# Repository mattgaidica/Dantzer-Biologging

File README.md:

# What is bio-logging?
The use of miniaturized, animal-borne bio-loggers to make physiological and environmental measurements from free-ranging animals is radically transforming scientific capabilities ([Williams et al., 2019](https://besjournals.onlinelibrary.wiley.com/doi/abs/10.1111/1365-2656.13094)). We have recently explored how to implement these technologies to expand the methods and resolution by which stress and performance are quantified in the wild ([Gaidica & Dantzer, 2019](https://ecoevorxiv.org/huxw6/)).

### Current Challenges
Bio-logging is historically niche due to the unique constraints of field biologists. From fish to birds, it is unreasonable to expect a one-size-fits-all solution. However, the ambitious goals of individuals *can and should* generalize to the bio-logging community under the following headings:

1. _Standardize_ data collection and analysis methods.
2. _Communicate_ approaches and insights.
3. _Innovate_ tools and technologies.

We are doing our best to make our projects **open source**. You can read more about our approach in [the Wiki](https://github.com/mattgaidica/biologging/wiki/Architecture).

## Why squirrels?

The ecological niche occupied by wild squirrels has been conserved for millions of years and is highlighted by their unique adaptations to arboreal life (i.e., in the trees). Their ability to regulate energy and maintain fitness through a variety of natural and imposed challenges ultimately determine their pedigree and survival. Little is known about how the central nervous system (CNS) is involved in these natural behaviors. One of our goals is to use bio-loggers to record from the CNS of wild squirrels to understand how their physiology and behavior are correlated, given the varying demands of their environment. Adding resolution to these important ecological factors is an important consideration to ongoing conservation work, potentially highlighting what ‘optimal adaptations’ are from a physiological perspective.

### Research Platform

Evolutionary pressures on wild animals engender advantageous platforms for study because behavior is so crucially linked with fitness. How mammalian physiology copes and adapts in response to changing environments is an important question that can benefit from the added resolution of bio-loggers. In addition to scientific investigations, the squirrel is a useful model to address many outstanding technical challenges—not unique to ecology—that make long-duration studies in harsh environments possible.

### Kluane Red Squirrel Project
[The Kluane Red Squirrel Project](https://redsquirrel.biology.ualberta.ca) (KRSP) is an interdisciplinary, large-scale field experiment located in the Canadian Yukon. KRSP has been collecting ecological and behavioral data on squirrels since 1987 and conducts a variety of studies and surveys on the population and food availability every year.

Squirrels in the Yukon face intense challenges including drastic changes in light/dark cycles through each season. During the summer months there is very little darkness (see image above). This natural rhythm makes KRSP and the squirrel an ideal candidate to study the affects of circadian entrainment.

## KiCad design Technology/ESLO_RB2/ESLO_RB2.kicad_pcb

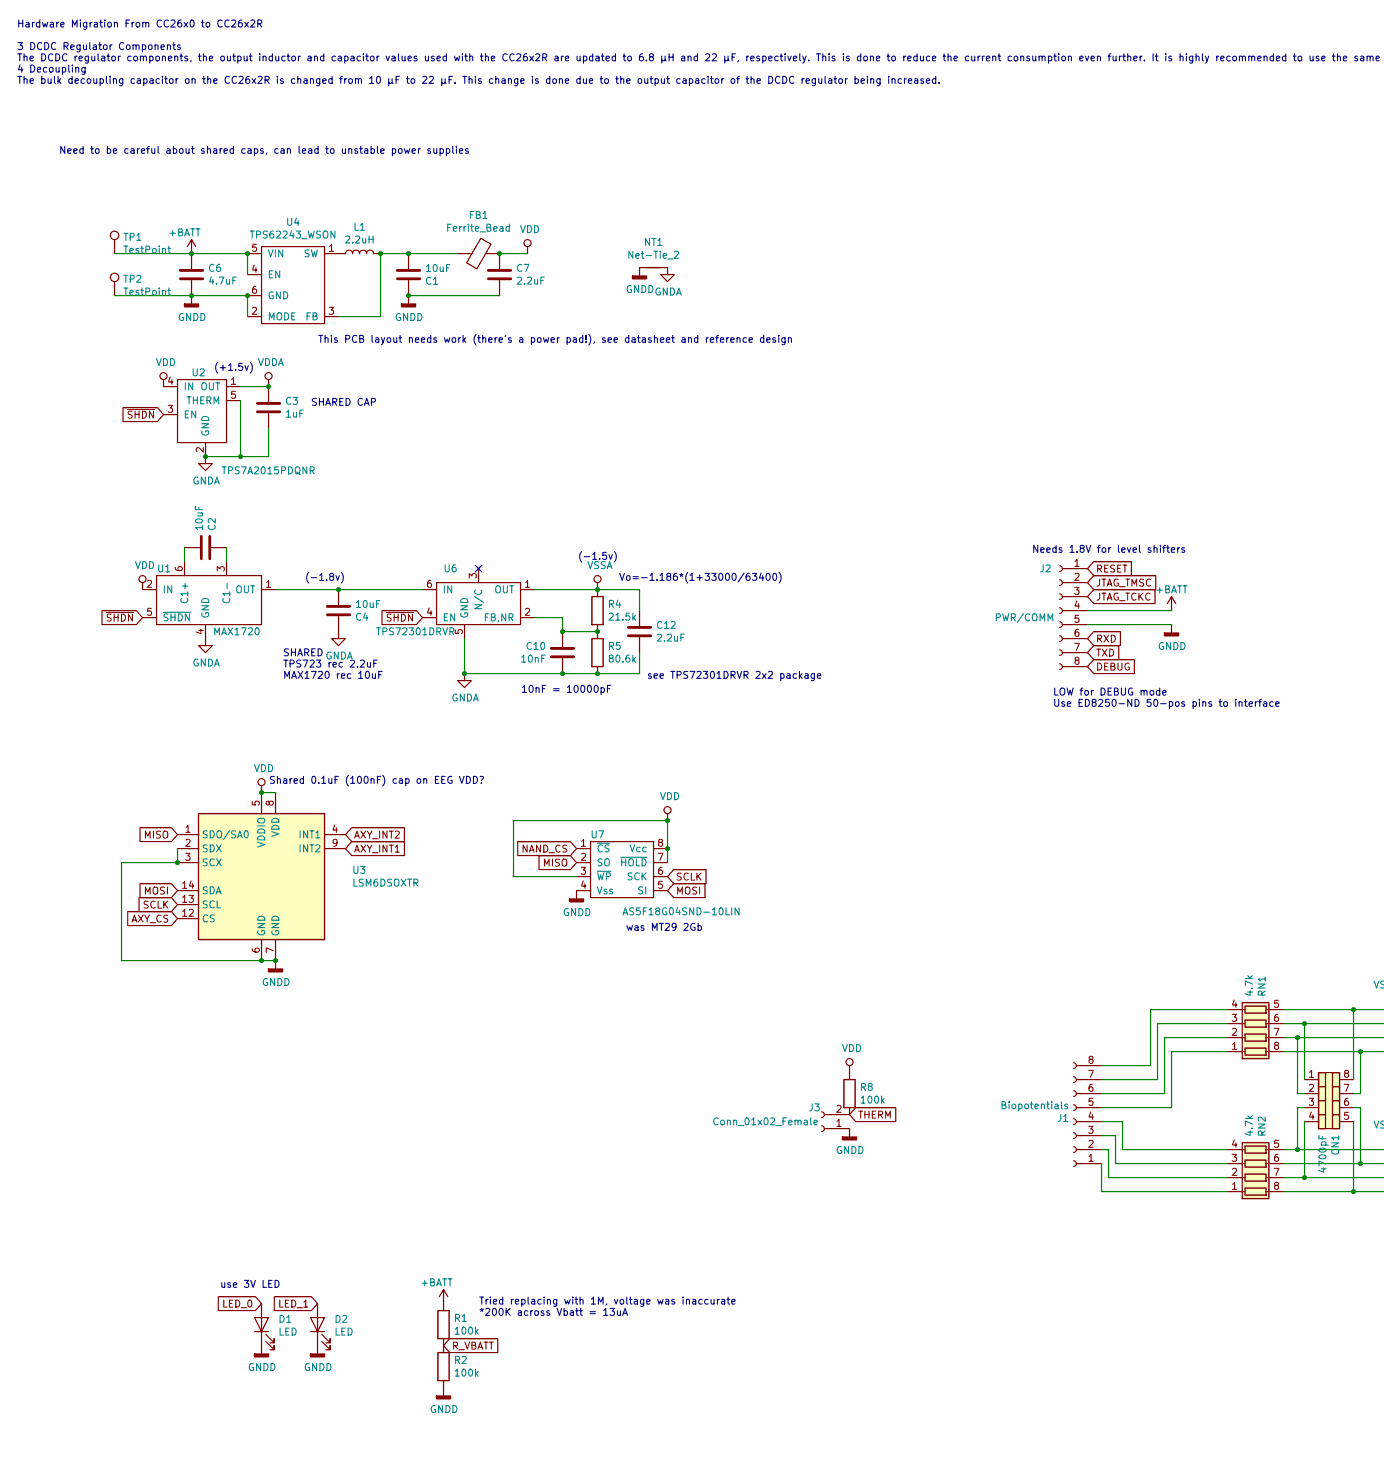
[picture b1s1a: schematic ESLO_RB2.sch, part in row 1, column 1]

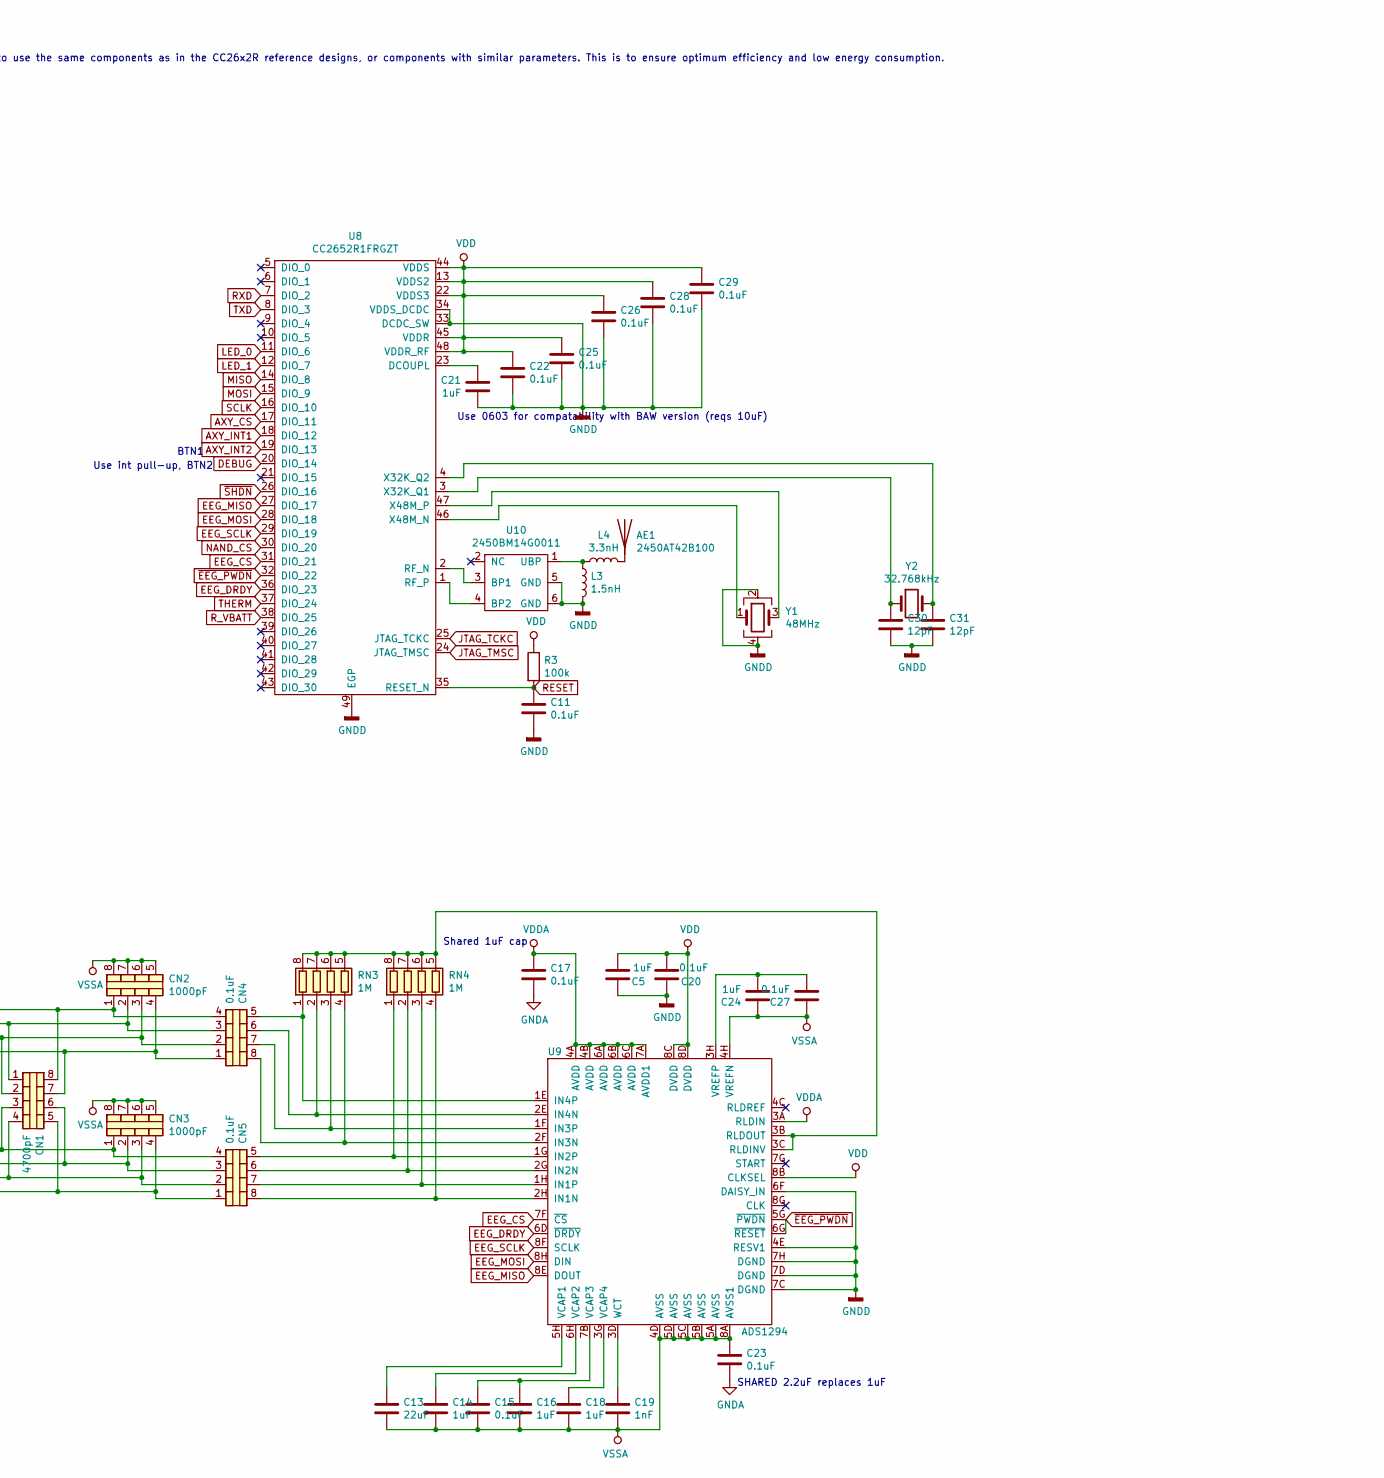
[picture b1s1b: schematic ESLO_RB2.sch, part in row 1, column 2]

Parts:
AE1: 2450AT42B100; Digikey 712-1008-1-ND‎
C1, C2, C4: 10uF; C_0603_1608Metric; Digikey 478-8050-1-ND
C3, C5, C14, C16, C18, C24: 1uF; C_0402_1005Metric; Digikey 399-4873-1-ND
C6: 4.7uF; C_0402_1005Metric; Digikey 1276-1484-2-ND
C7, C12: 2.2uF; C_0402_1005Metric; Digikey 1253-CM05X5R225K10AHCT-ND
C10: 10nF; C_0402_1005Metric; Digikey 1276-1051-1-ND
C11, C15, C17, C20, C22, C23, C25, C26, C27, C28, C29: 0.1uF; C_0402_1005Metric; Digikey 490-6328-1-ND
C13: 22uF; C_0603_1608Metric; Digikey 490-7611-1-ND
C19: 1nF; C_0402_1005Metric; Digikey 478-1101-1-ND
C21: 1uF; C_0603_1608Metric; Digikey 399-7847-2-ND
C30, C31: 12pF; C_0402_1005Metric; Digikey 490-5924-2-ND
CN1: 4700pF; 0612_array; Digikey 399-CA064X473K4RACTUTR-ND
CN2, CN3: 1000pF; 0508_array; Digikey 399-12980-1-ND
CN4, CN5: 0.1uF; 0508_array; Digikey 478-7584-2-ND
D1: LED; LED_0402_1005Metric; Digikey VLMB1500-GS08CT-ND
D2: LED; LED_0402_1005Metric; Digikey VLMO1500-GS08CT-ND
FB1: Ferrite_Bead; C_0603_1608Metric; Digikey 490-5216-2-ND
J1: Biopotentials; ESLO_IO_8_1-27; Digikey ED8250-ND
J2: PWR/COMM; ESLO_IO_8_1-27; Digikey ED90570-ND
J3: Conn_01x02_Female; ESLO_2pin_THERM
L1: 2.2uH; L_0805_2012Metric; Digikey 490-4994-2-ND
L3: 1.5nH; L_0402_1005Metric; Digikey 334-1083-2-ND
L4: 3.3nH; L_0402_1005Metric; Digikey 712-1416-1-ND
NT1: Net-Tie_2; NetTie-2_SMD_Pad0.5mm
R1, R2, R3, R8: 100k; LED_0402_1005Metric; Digikey 311-100KLRCT-ND
R4: 21.5k; R_0402_1005Metric; Digikey RMCF0402FT21K5CT-ND
R5: 80.6k; R_0402_1005Metric; Digikey RMCF0402FT80K6CT-ND
RN1, RN2: 4.7k; 0502_array; Digikey Y6472CT-ND
RN3, RN4: 1M; 0502_array; Digikey Y6105CT-ND
TP1: TestPoint; Half2032Clip_BC-2003; Digikey 36-3036-ND
TP2: TestPoint; 5015_TP; Digikey 36-5015TR-ND
U1: MAX1720; SOT-23-6; Digikey MAX1720EUTGOSCT-ND
U2: TPS7A2015PDQNR; Texas_X2SON-4_1x1mm_P0.65mm; Digikey 296-TPS7A2015PDQNRTR-ND
U3: LSM6DSOXTR; LGA-14_3x2.5mm_P0.5mm_LayoutBorder3x4y; Digikey 497-18367-2-ND
U4: TPS62243_WSON; WSON-6-1EP_2x2mm_P0.65mm_EP1x1.6mm; Digikey 296-46476-1-ND
U6: TPS72301DRVR; WSON-6-1EP_2x2mm_P0.65mm_EP1x1.6mm; Digikey 296-TPS72301DRVRTR-ND
U7: AS5F18G04SND-10LIN; 8x6mm_WSON_UTSO; Digikey 1450-AS5F18G04SND-10LIN-ND
U8: CC2652R1FRGZT; QFN-48-1EP_7x7mm_P0.5mm_EP5.15x5.15mm; Mouser 595-CC2652R1FRGZR
U9: ADS1294; BGA-64_8x8_8.0x8.0mm_ADS129x; Digikey 296-28024-1-ND
U10: 2450BM14G0011; Digikey 712-1620-1-ND
Y1: 48MHz; Crystal_SMD_2016-4Pin_2.0x1.6mm; Digikey 535-13927-2-ND
Y2: 32.768kHz; Crystal_SMD_2012-2Pin_2.0x1.2mm; Digikey SER4081TR-ND

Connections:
+BATT: C6.1, J2.4, R1.1, TP1.1, U4.4 (EN), U4.5 (VIN)
AXY_CS: U3.12 (CS), U8.17 (DIO_11)
AXY_INT1: U3.9 (INT2), U8.18 (DIO_12)
AXY_INT2: U3.4 (INT1), U8.19 (DIO_13)
DEBUG: J2.8, U8.20 (DIO_14)
EEG_CS: U8.31 (DIO_21), U9.7F (~CS)
EEG_DRDY: U8.36 (DIO_23), U9.6D (~DRDY)
EEG_MISO: U8.27 (DIO_17), U9.8E (DOUT)
EEG_MOSI: U8.28 (DIO_18), U9.8H (DIN)
EEG_SCLK: U8.29 (DIO_19), U9.8F (SCLK)
GNDA: C3.2, C4.2, C10.1, C12.2, C17.2, C23.2, NT1.2, R5.2, U1.4 (GND), U2.2 (GND), U2.5 (THERM), U6.5 (GND)
GNDD: C1.2, C5.1, C6.2, C7.2, C11.2, C20.1, C21.1, C22.2, C25.2, C26.2, C28.2, C29.2, C30.2, C31.2, D1.1 (K), D2.1 (K), J2.5, J3.1, L3.2, NT1.1, R2.2, TP2.1, U3.2 (SDX), U3.3 (SCX), U3.6 (GND), U3.7 (GND), U4.2 (MODE), U4.6 (GND), U7.4 (Vss), U8.33 (DCDC_SW), U8.34 (VDDS_DCDC), U8.49 (EGP), U9.4E (RESV1), U9.6F (DAISY_IN), U9.7C (DGND), U9.7D (DGND), U9.7H (DGND), U10.5 (GND), U10.6 (GND), Y1.2, Y1.4
JTAG_TCKC: J2.3, U8.25 (JTAG_TCKC)
JTAG_TMSC: J2.2, U8.24 (JTAG_TMSC)
LED_0: D1.2 (A), U8.11 (DIO_6)
LED_1: D2.2 (A), U8.12 (DIO_7)
MISO: U3.1 (SDO/SA0), U7.2 (SO), U8.14 (DIO_8)
MOSI: U3.14 (SDA), U7.5 (SI), U8.15 (DIO_9)
NAND_CS: U7.1 (~CS), U8.30 (DIO_20)
unnamed: AE1.1, L4.2
unnamed: C1.1, FB1.2, L1.2, U4.3 (FB)
unnamed: C2.1, U1.6 (C1+)
unnamed: C2.2, U1.3 (C1-)
unnamed: C4.1, U1.1 (OUT), U6.6 (IN)
unnamed: C10.2, R4.2, R5.1, U6.2 (FB,NR)
unnamed: C13.1, U9.5H (VCAP1)
unnamed: C14.1, U9.6H (VCAP2)
unnamed: C15.1, C16.1, U9.7B (VCAP3)
unnamed: C18.1, U9.3G (VCAP4)
unnamed: C19.1, U9.3D (WCT)
unnamed: C21.2, U8.23 (DCOUPL)
unnamed: C24.2, C27.2, U9.3H (VREFP)
unnamed: C30.1, U8.3 (X32K_Q1), Y2.1
unnamed: C31.1, U8.4 (X32K_Q2), Y2.2
unnamed: CN1.1 (C1.1), CN2.2 (C2.1), CN4.3 (C3.1), RN1.6 (R3.2)
unnamed: CN1.2 (C2.1), CN2.3 (C3.1), CN4.2 (C2.1), RN1.7 (R2.2)
unnamed: CN1.3 (C3.1), CN3.1 (C1.1), CN5.4 (C4.1), RN2.5 (R4.2)
unnamed: CN1.4 (C4.1), CN3.3 (C3.1), CN5.2 (C2.1), RN2.7 (R2.2)
unnamed: CN1.5 (C4.2), CN3.4 (C4.1), CN5.1 (C1.1), RN2.8 (R1.2)
unnamed: CN1.6 (C3.2), CN3.2 (C2.1), CN5.3 (C3.1), RN2.6 (R3.2)
unnamed: CN1.7 (C2.2), CN2.4 (C4.1), CN4.1 (C1.1), RN1.8 (R1.2)
unnamed: CN1.8 (C1.2), CN2.1 (C1.1), CN4.4 (C4.1), RN1.5 (R4.2)
unnamed: CN4.5 (C4.2), RN3.1 (R1.1), U9.1E (IN4P)
unnamed: CN4.6 (C3.2), RN3.2 (R2.1), U9.2E (IN4N)
unnamed: CN4.7 (C2.2), RN3.3 (R3.1), U9.1F (IN3P)
unnamed: CN4.8 (C1.2), RN3.4 (R4.1), U9.2F (IN3N)
unnamed: CN5.5 (C4.2), RN4.1 (R1.1), U9.1G (IN2P)
unnamed: CN5.6 (C3.2), RN4.2 (R2.1), U9.2G (IN2N)
unnamed: CN5.7 (C2.2), RN4.3 (R3.1), U9.1H (IN1P)
unnamed: CN5.8 (C1.2), RN4.4 (R4.1), U9.2H (IN1N)
unnamed: J1.1, RN2.1 (R1.1)
unnamed: J1.2, RN2.2 (R2.1)
unnamed: J1.3, RN2.3 (R3.1)
unnamed: J1.4, RN2.4 (R4.1)
unnamed: J1.5, RN1.1 (R1.1)
unnamed: J1.6, RN1.2 (R2.1)
unnamed: J1.7, RN1.3 (R3.1)
unnamed: J1.8, RN1.4 (R4.1)
unnamed: L1.1, U4.1 (SW)
unnamed: L3.1, L4.1, U10.1 (UBP)
unnamed: RN3.5 (R4.2), RN3.6 (R3.2), RN3.7 (R2.2), RN3.8 (R1.2), RN4.5 (R4.2), RN4.6 (R3.2), RN4.7 (R2.2), RN4.8 (R1.2), U9.3B (RLDOUT), U9.3C (RLDINV)
unnamed: U8.46 (X48M_N), Y1.1
unnamed: U8.47 (X48M_P), Y1.3
unnamed: U8.2 (RF_N), U10.3 (BP1)
unnamed: U8.1 (RF_P), U10.4 (BP2)
RESET: C11.1, J2.1, R3.2, U8.35 (RESET_N)
RXD: J2.6, U8.7 (DIO_2)
R_VBATT: R1.2, R2.1, U8.38 (DIO_25)
SCLK: U3.13 (SCL), U7.6 (SCK), U8.16 (DIO_10)
THERM: J3.2, R8.2, U8.37 (DIO_24)
TXD: J2.7, U8.8 (DIO_3)
VDD: C5.2, C7.1, C20.2, C22.1, C25.1, C26.1, C28.1, C29.1, FB1.1, R3.1, R8.1, U1.2 (IN), U2.4 (IN), U3.5 (VDDIO), U3.8 (VDD), U7.3 (~WP), U7.7 (~HOLD), U7.8 (Vcc), U8.13 (VDDS2), U8.22 (VDDS3), U8.44 (VDDS), U8.45 (VDDR), U8.48 (VDDR_RF), U9.8B (CLKSEL), U9.8C (DVDD), U9.8D (DVDD)
VDDA: C3.1, C17.1, U2.1 (OUT), U9.3A (RLDIN), U9.4A (AVDD), U9.4B (AVDD), U9.6A (AVDD), U9.6B (AVDD), U9.6C (AVDD), U9.7A (AVDD1)
VSSA: C12.1, C13.2, C14.2, C15.2, C16.2, C18.2, C19.2, C23.1, C24.1, C27.1, CN2.5 (C4.2), CN2.6 (C3.2), CN2.7 (C2.2), CN2.8 (C1.2), CN3.5 (C4.2), CN3.6 (C3.2), CN3.7 (C2.2), CN3.8 (C1.2), R4.1, U6.1 (OUT), U9.4D (AVSS), U9.4H (VREFN), U9.5A (AVSS), U9.5B (AVSS), U9.5C (AVSS), U9.5D (AVSS), U9.8A (AVSS1)
~EEG_PWDN: U8.32 (DIO_22), U9.5G (~PWDN), U9.6G (~RESET)
~SHDN: U1.5 (~SHDN), U2.3 (EN), U6.4 (EN), U8.26 (DIO_16)

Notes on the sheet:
Vo=-1.186*(1+33000/63400)
(-1.5v)
(+1.5v)
(-1.8v)
SHARED TPS723 rec 2.2uF MAX1720 rec 10uF
SHARED CAP
BTN1
Shared 1uF cap
SHARED 2.2uF replaces 1uF
Use int pull-up, BTN2
LOW for DEBUG mode Use ED8250-ND 50-pos pins to interface
Needs 1.8V for level shifters
10nF = 10000pF
Tried replacing with 1M, voltage was inaccurate *200K across Vbatt = 13uA
see TPS72301DRVR 2x2 package
Hardware Migration From CC26x0 to CC26x2R 3 DCDC Regulator Components The DCDC regulator components, the output inductor and capacitor values used with the CC26x2R are updated to 6.8 μH and 22 μF, respectively. This is done to reduce the current consumption even further. It is highly recommended to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
was MT29 2Gb
use 3V LED
Shared 0.1uF (100nF) cap on EEG VDD?
Use 0603 for compatability with BAW version (reqs 10uF)
This PCB layout needs work (there’s a power pad!), see datasheet and reference design
Need to be careful about shared caps, can lead to unstable power supplies

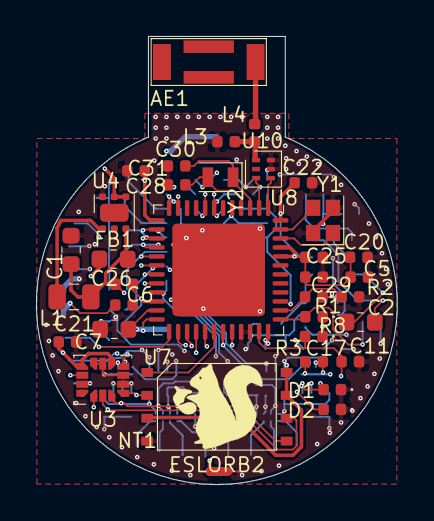
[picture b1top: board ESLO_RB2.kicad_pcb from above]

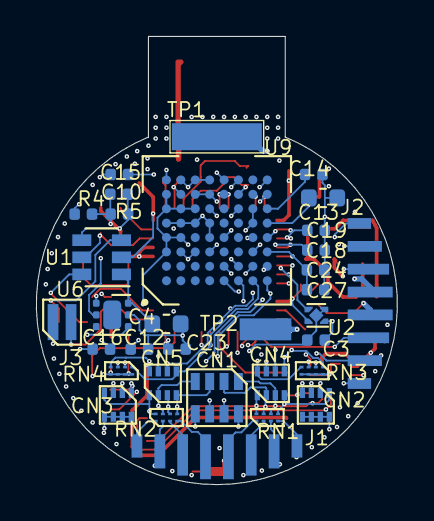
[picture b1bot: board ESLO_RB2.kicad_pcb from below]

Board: 4 copper layers, 20.0 x 24.9 mm, 68 parts (33 on the bottom side), 76 nets.

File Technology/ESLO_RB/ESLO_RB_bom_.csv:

Component,Description,Part,References,Value,Footprint,Quantity Per PCB,Datasheet,Digikey,Mouser
1,Antenna,Antenna,AE1,2450AT42B100,2450AT42B100,1,~,712-1008-1-ND‎,
2,Unpolarized capacitor,C,C3 C11 C15 C17 C20 C22 C23 C25 C26 C27 C28 C29,0.1uF,C_0402_1005Metric,12,~,490-6328-1-ND,
3,Unpolarized capacitor,C,C7,0.22uF,C_0402_1005Metric,1,~,1276-1176-1-ND,
4,Unpolarized capacitor,C,C10,10nF,C_0402_1005Metric,1,~,1276-1051-1-ND,
5,Unpolarized capacitor,C,C1 C2 C4 C6,10uF,C_0603_1608Metric,4,~,490-14372-1-ND,
6,Unpolarized capacitor,C,C19,1nF,C_0402_1005Metric,1,~,478-1101-1-ND,
7,Unpolarized capacitor,C,C5 C9 C14 C16 C18 C21 C24,1uF,C_0402_1005Metric,7,~,399-4873-1-ND,
8,Unpolarized capacitor,C,C8 C12,2.2uF,C_0402_1005Metric,2,~,1276-1469-1-ND,
9,Unpolarized capacitor,C,C13,22uF,C_0603_1608Metric,1,~,1276-2867-1-ND,
10,"4 capacitor network, parallel topology, DIP package",C_Pack04,CN2 CN3,1000pF,0508_array,2,~,478-W2A45C102KAT2ACT-ND,
11,"4 capacitor network, parallel topology, DIP package",C_Pack04,CN4 CN5,1uF,0508_array,2,~,,581-W2L16D105MAT1A
12,"4 capacitor network, parallel topology, DIP package",C_Pack04,CN1,4700pF,0508_array,1,~,,581-W2A41C472KAT2A
13,Light emitting diode,LED,D1,LED,LED_0603_1608Metric,1,~,SML-D12V1WT86CT-ND,
14,"Generic connector, single row, 01x10, script generated (kicad-library-utils/schlib/autogen/connector/)",Conn_01x10_Female,J1,10POS Biopotentials,ARBO_IO10_1.27mm,1,~,ED10276-ND,
15,"Generic connector, single row, 01x06, script generated (kicad-library-utils/schlib/autogen/connector/)",Conn_01x06_Female,J2,6POS Power/JTAG,ARBO_IO6_1.27mm,1,~,ED10273-ND,
16,Inductor,L,L3,1.5nH,L_0402_1005Metric,1,~,712-1411-1-ND,
17,Inductor,L,L1,2.2uH,L_0805_2012Metric,1,~,490-7781-1-ND,
18,Inductor,L,L4,3.3nH,L_0402_1005Metric,1,~,712-1416-1-ND,
19,Inductor,L,L2,BLM18HE152SN1,L_0603_1608Metric,1,~,490-5216-1-ND,
20,"Net tie, 2 pins",Net-Tie_2,NT1,Net-Tie_2,NetTie-2_SMD_Pad0.5mm,1,~,,
21,Resistor,R,R1 R2 R3 R8,100k,LED_0402_1005Metric,4,~,311-100KLRCT-ND,
22,Resistor,R,R4,21.5k,R_0402_1005Metric,1,~,RMCF0402FT21K5CT-ND,
23,Resistor,R,R6 R7,4.7k,R_0402_1005Metric,2,~,311-4.7KJRCT-ND,
24,Resistor,R,R5,80.6k,R_0402_1005Metric,1,~,RMCF0402FT80K6CT-ND,
25,"4 resistor network, parallel topology, DIP package",R_Pack04,RN3 RN4,1M,0502_array,2,~,Y6105CT-ND,
26,"4 resistor network, parallel topology, DIP package",R_Pack04,RN1 RN2,4.7k,0502_array,2,~,Y6472CT-ND,
27,,2450BM14G0011,U10,2450BM14G0011,2450BM14G0011,1,,712-1620-1-ND,
28,,ADS1294,U9,ADS1294,BGA-64_8x8_8.0x8.0mm_ADS129x,1,,296-28024-1-ND,
29,,CC2652RB,U8,CC2652RB,QFN-48-1EP_7x7mm_P0.5mm_EP5.15x5.15mm,1,,296-CC2652RB1FRGZRCT-ND,
30,"FRAM memory with SPI interface, SOIC-8 SON-8",MB85RS2MT,U3,CY15V104QI-20LPXC,8-GQFN_FRAM_3.28mm-3.23mm,1,http://www.fujitsu.com/downloads/MICRO/fsa/pdf/products/memo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,428-4724-ND,
31,"250-mA Ultra-Low-Noise Low-IQ LDO, 1.8V, SOT-23",LP5907MFX-1.8,U5,LP5907MFX-1.5,SOT-23-5,1,http://www.ti.com/lit/ds/symlink/lp5907.pdf,296-40355-1-ND,
32,,LSM303AGR,U4,LSM303AGR,LGA-12_2x2mm_P0.5mm,1,,497-16527-1-ND,
33,,MAX1720,U1,MAX1720,SOT-23-6,1,,MAX1720EUTGOSCT-ND,
34,,IS37SML01G1,U7,MT29F2G01ABBGDWB-IT:G TR,8x6mm_WSON_UTSO,1,,557-1665-1-ND,
35,,TPS62740,U2,TPS62740,WSON-12-1EP_3x2mm_P0.5mm_EP1x2.65,1,,296-39459-1-ND,
36,,TPS72325,U6,TPS72301DDCT,SOT-23-5,1,,296-38438-1-ND,





Component Groups:,36
Component Count:,65
Fitted Components:,65
Number of PCBs:,1
Total components:,65
Schematic Version:,
Schematic Date:,
BoM Date:,"Friday, June 04, 2021 at 01:24:00 PM"
Schematic Source:,/Users/matt/Box Sync/Biologging/Technology/ESLO_RB/ESLO_RB.sch
KiCad Version:,Eeschema (5.1.5-0-10_14)

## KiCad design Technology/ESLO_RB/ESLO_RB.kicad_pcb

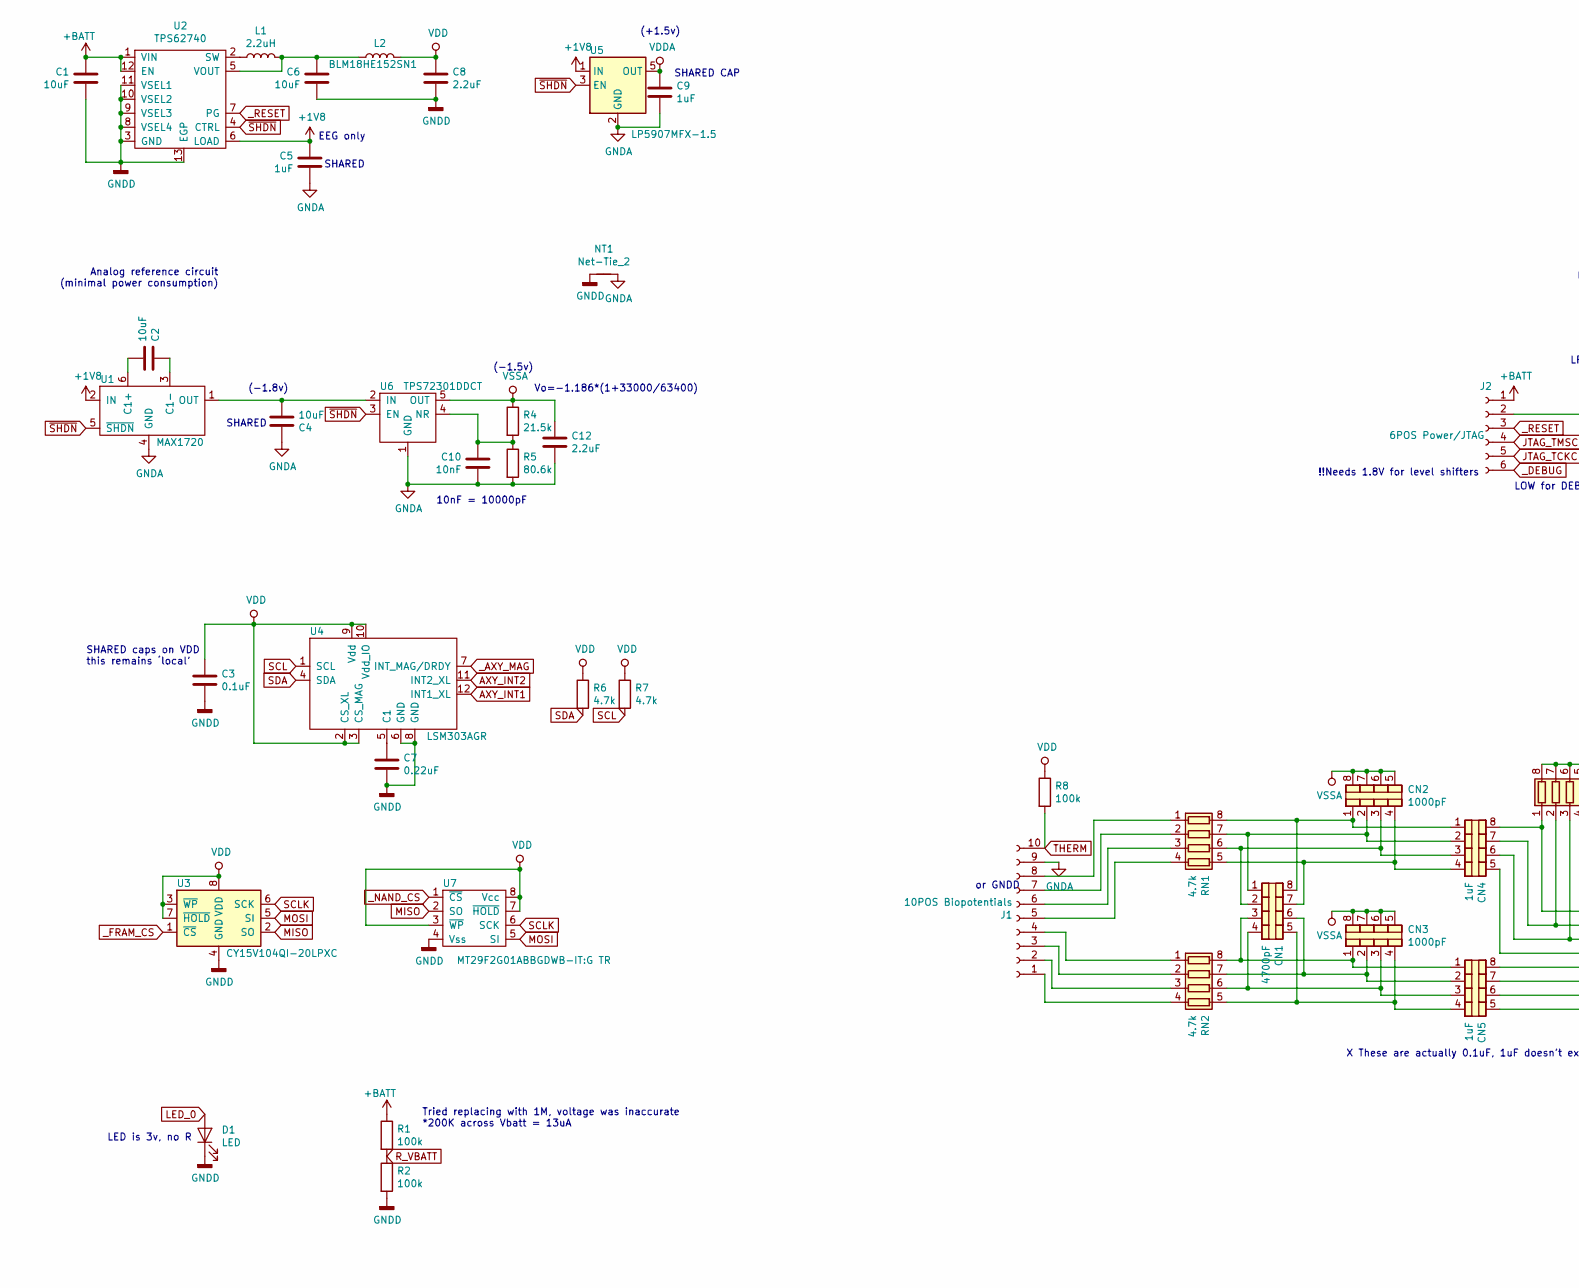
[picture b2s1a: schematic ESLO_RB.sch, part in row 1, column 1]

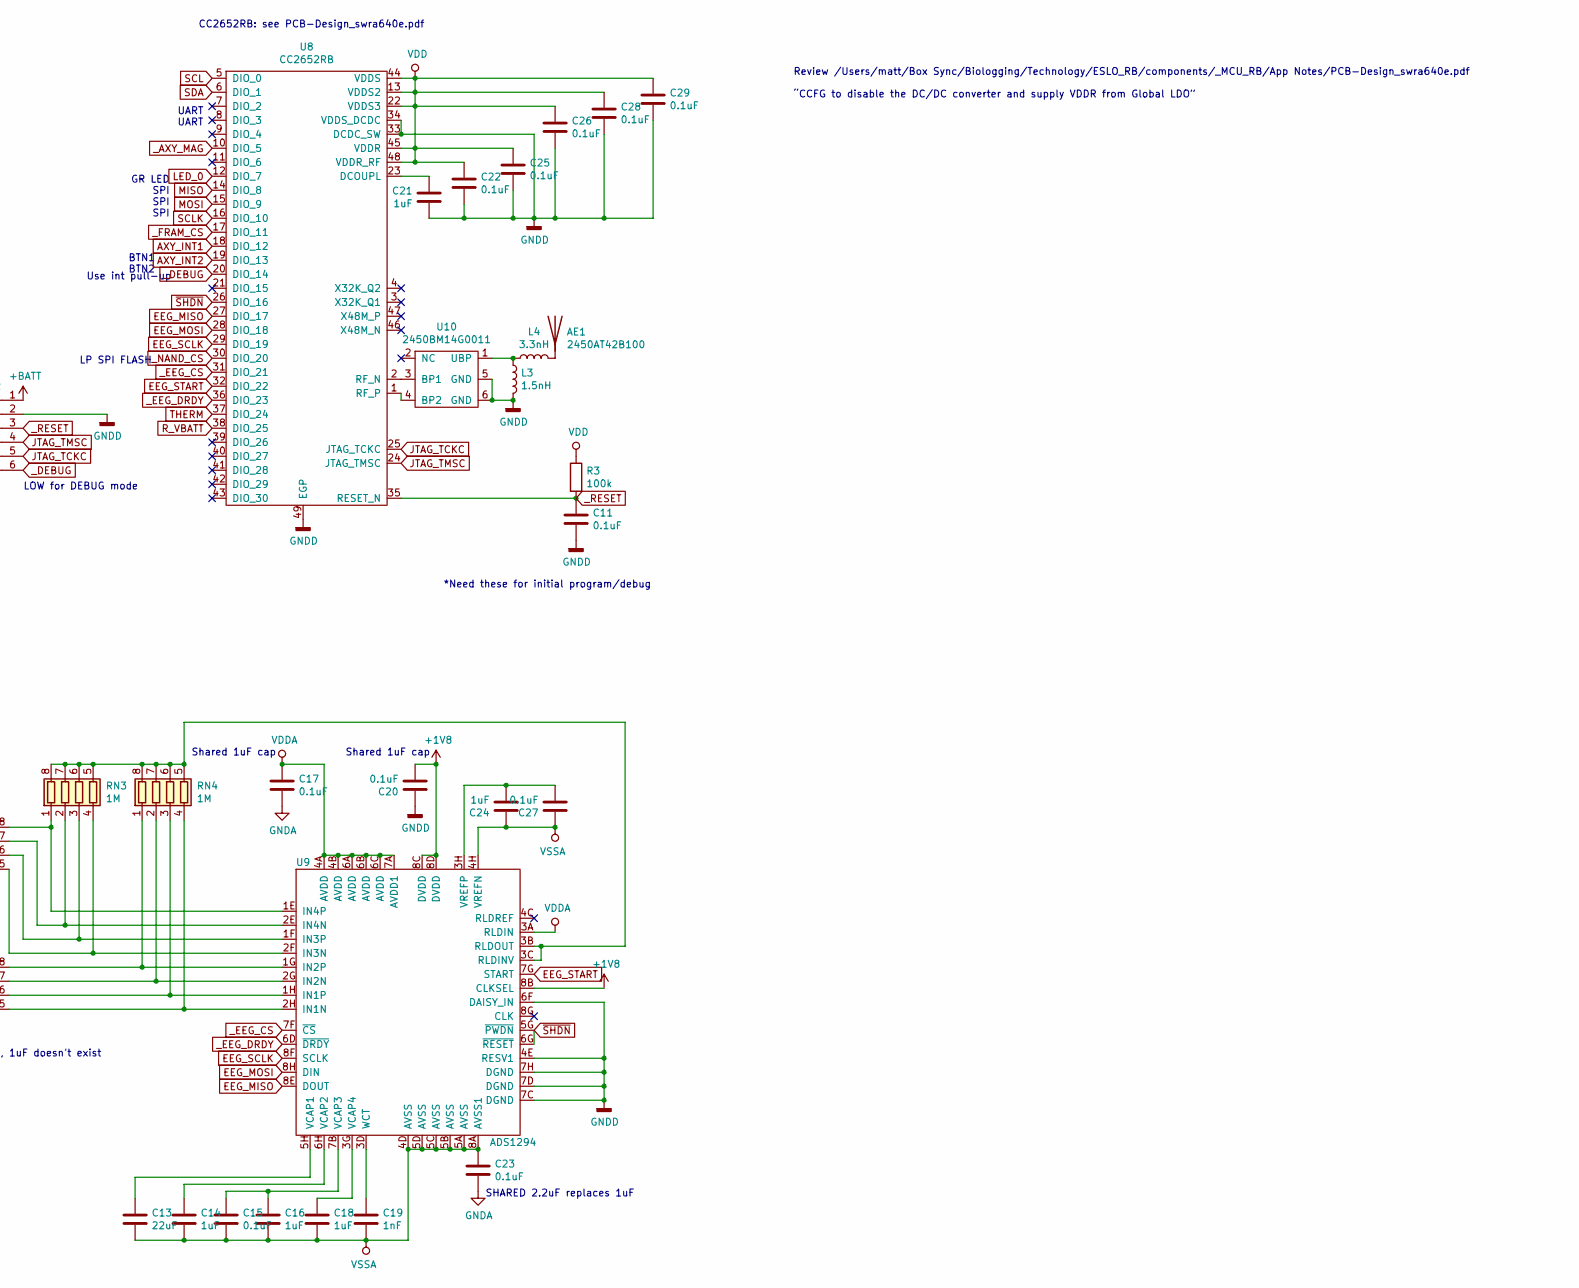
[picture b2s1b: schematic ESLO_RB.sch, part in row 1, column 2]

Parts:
AE1: 2450AT42B100; Digikey 712-1008-1-ND‎
C1, C2, C4, C6: 10uF; C_0603_1608Metric; Digikey 490-14372-1-ND
C3, C11, C15, C17, C20, C22, C23, C25, C26, C27, C28, C29: 0.1uF; C_0402_1005Metric; Digikey 490-6328-1-ND
C5, C9, C14, C16, C18, C21, C24: 1uF; C_0402_1005Metric; Digikey 399-4873-1-ND
C7: 0.22uF; C_0402_1005Metric; Digikey 1276-1176-1-ND
C8, C12: 2.2uF; C_0402_1005Metric; Digikey 1276-1469-1-ND
C10: 10nF; C_0402_1005Metric; Digikey 1276-1051-1-ND
C13: 22uF; C_0603_1608Metric; Digikey 1276-2867-1-ND
C19: 1nF; C_0402_1005Metric; Digikey 478-1101-1-ND
CN1: 4700pF; 0508_array; Mouser 581-W2A41C472KAT2A
CN2, CN3: 1000pF; 0508_array; Digikey 478-W2A45C102KAT2ACT-ND
CN4, CN5: 1uF; 0508_array; Mouser 581-W2L16D105MAT1A
D1: LED; LED_0603_1608Metric; Digikey SML-D12V1WT86CT-ND
J1: 10POS Biopotentials; ARBO_IO10_1.27mm; Digikey ED10276-ND
J2: 6POS Power/JTAG; ARBO_IO6_1.27mm; Digikey ED10273-ND
L1: 2.2uH; L_0805_2012Metric; Digikey 490-7781-1-ND
L2: BLM18HE152SN1; L_0603_1608Metric; Digikey 490-5216-1-ND
L3: 1.5nH; L_0402_1005Metric; Digikey 712-1411-1-ND
L4: 3.3nH; L_0402_1005Metric; Digikey 712-1416-1-ND
NT1: Net-Tie_2; NetTie-2_SMD_Pad0.5mm
R1, R2, R3, R8: 100k; LED_0402_1005Metric; Digikey 311-100KLRCT-ND
R4: 21.5k; R_0402_1005Metric; Digikey RMCF0402FT21K5CT-ND
R5: 80.6k; R_0402_1005Metric; Digikey RMCF0402FT80K6CT-ND
R6, R7: 4.7k; R_0402_1005Metric; Digikey 311-4.7KJRCT-ND
RN1, RN2: 4.7k; 0502_array; Digikey Y6472CT-ND
RN3, RN4: 1M; 0502_array; Digikey Y6105CT-ND
U1: MAX1720; SOT-23-6; Digikey MAX1720EUTGOSCT-ND
U2: TPS62740; WSON-12-1EP_3x2mm_P0.5mm_EP1x2.65; Digikey 296-39459-1-ND
U3: CY15V104QI-20LPXC; 8-GQFN_FRAM_3.28mm-3.23mm; Digikey 428-4724-ND
U4: LSM303AGR; LGA-12_2x2mm_P0.5mm; Digikey 497-16527-1-ND
U5: LP5907MFX-1.5; SOT-23-5; Digikey 296-40355-1-ND
U6: TPS72301DDCT; SOT-23-5; Digikey 296-38438-1-ND
U7: MT29F2G01ABBGDWB-IT:G TR; 8x6mm_WSON_UTSO; Digikey 557-1665-1-ND
U8: CC2652RB; QFN-48-1EP_7x7mm_P0.5mm_EP5.15x5.15mm; Digikey 296-CC2652RB1FRGZRCT-ND
U9: ADS1294; BGA-64_8x8_8.0x8.0mm_ADS129x; Digikey 296-28024-1-ND
U10: 2450BM14G0011; Digikey 712-1620-1-ND

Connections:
+1V8: C5.2, C20.2, U1.2 (IN), U2.6 (LOAD), U5.1 (IN), U9.8B (CLKSEL), U9.8C (DVDD), U9.8D (DVDD)
+BATT: C1.2, J2.1, R1.1, U2.1 (VIN), U2.12 (EN)
AXY_INT1: U4.12 (INT1_XL), U8.18 (DIO_12)
AXY_INT2: U4.11 (INT2_XL), U8.19 (DIO_13)
EEG_MISO: U8.27 (DIO_17), U9.8E (DOUT)
EEG_MOSI: U8.28 (DIO_18), U9.8H (DIN)
EEG_SCLK: U8.29 (DIO_19), U9.8F (SCLK)
EEG_START: U8.32 (DIO_22), U9.7G (START)
GNDA: C4.2, C5.1, C9.2, C10.1, C12.2, C17.2, C23.2, J1.9, NT1.2, R5.2, U1.4 (GND), U5.2 (GND), U6.1 (GND)
GNDD: C1.1, C3.2, C6.1, C7.1, C8.2, C11.2, C20.1, C21.1, C22.2, C25.2, C26.2, C28.2, C29.2, D1.1 (K), J2.2, L3.2, NT1.1, R2.2, U2.3 (GND), U2.8 (VSEL4), U2.9 (VSEL3), U2.10 (VSEL2), U2.11 (VSEL1), U2.13 (EGP), U3.4 (GND), U4.6 (GND), U4.8 (GND), U7.4 (Vss), U8.33 (DCDC_SW), U8.34 (VDDS_DCDC), U8.49 (EGP), U9.4E (RESV1), U9.6F (DAISY_IN), U9.7C (DGND), U9.7D (DGND), U9.7H (DGND), U10.5 (GND), U10.6 (GND)
JTAG_TCKC: J2.5, U8.25 (JTAG_TCKC)
JTAG_TMSC: J2.4, U8.24 (JTAG_TMSC)
LED_0: D1.2 (A), U8.12 (DIO_7)
MISO: U3.2 (SO), U7.2 (SO), U8.14 (DIO_8)
MOSI: U3.5 (SI), U7.5 (SI), U8.15 (DIO_9)
unnamed: AE1.1, L4.2
unnamed: C2.1, U1.6 (C1+)
unnamed: C2.2, U1.3 (C1-)
unnamed: C4.1, U1.1 (OUT), U6.2 (IN)
unnamed: C6.2, L1.2, L2.1, U2.5 (VOUT)
unnamed: C7.2, U4.5 (C1)
unnamed: C10.2, R4.2, R5.1, U6.4 (NR)
unnamed: C13.1, U9.5H (VCAP1)
unnamed: C14.1, U9.6H (VCAP2)
unnamed: C15.1, C16.1, U9.7B (VCAP3)
unnamed: C18.1, U9.3G (VCAP4)
unnamed: C19.1, U9.3D (WCT)
unnamed: C21.2, U8.23 (DCOUPL)
unnamed: C24.2, C27.2, U9.3H (VREFP)
unnamed: CN1.1 (C1.1), CN2.2 (C2.1), CN4.2 (C2.1), RN1.7 (R2.2)
unnamed: CN1.2 (C2.1), CN2.3 (C3.1), CN4.3 (C3.1), RN1.6 (R3.2)
unnamed: CN1.3 (C3.1), CN3.1 (C1.1), CN5.1 (C1.1), RN2.8 (R1.2)
unnamed: CN1.4 (C4.1), CN3.3 (C3.1), CN5.3 (C3.1), RN2.6 (R3.2)
unnamed: CN1.5 (C4.2), CN3.4 (C4.1), CN5.4 (C4.1), RN2.5 (R4.2)
unnamed: CN1.6 (C3.2), CN3.2 (C2.1), CN5.2 (C2.1), RN2.7 (R2.2)
unnamed: CN1.7 (C2.2), CN2.4 (C4.1), CN4.4 (C4.1), RN1.5 (R4.2)
unnamed: CN1.8 (C1.2), CN2.1 (C1.1), CN4.1 (C1.1), RN1.8 (R1.2)
unnamed: CN4.5 (C4.2), RN3.4 (R4.1), U9.2F (IN3N)
unnamed: CN4.6 (C3.2), RN3.3 (R3.1), U9.1F (IN3P)
unnamed: CN4.7 (C2.2), RN3.2 (R2.1), U9.2E (IN4N)
unnamed: CN4.8 (C1.2), RN3.1 (R1.1), U9.1E (IN4P)
unnamed: CN5.5 (C4.2), RN4.4 (R4.1), U9.2H (IN1N)
unnamed: CN5.6 (C3.2), RN4.3 (R3.1), U9.1H (IN1P)
unnamed: CN5.7 (C2.2), RN4.2 (R2.1), U9.2G (IN2N)
unnamed: CN5.8 (C1.2), RN4.1 (R1.1), U9.1G (IN2P)
unnamed: J1.1, RN2.4 (R4.1)
unnamed: J1.2, RN2.3 (R3.1)
unnamed: J1.3, RN2.2 (R2.1)
unnamed: J1.4, RN2.1 (R1.1)
unnamed: J1.5, RN1.4 (R4.1)
unnamed: J1.6, RN1.3 (R3.1)
unnamed: J1.7, RN1.2 (R2.1)
unnamed: J1.8, RN1.1 (R1.1)
unnamed: L1.1, U2.2 (SW)
unnamed: L3.1, L4.1, U10.1 (UBP)
unnamed: RN3.5 (R4.2), RN3.6 (R3.2), RN3.7 (R2.2), RN3.8 (R1.2), RN4.5 (R4.2), RN4.6 (R3.2), RN4.7 (R2.2), RN4.8 (R1.2), U9.3B (RLDOUT), U9.3C (RLDINV)
unnamed: U8.2 (RF_N), U10.3 (BP1)
unnamed: U8.1 (RF_P), U10.4 (BP2)
R_VBATT: R1.2, R2.1, U8.38 (DIO_25)
SCL: R7.2, U4.1 (SCL), U8.5 (DIO_0)
SCLK: U3.6 (SCK), U7.6 (SCK), U8.16 (DIO_10)
SDA: R6.2, U4.4 (SDA), U8.6 (DIO_1)
THERM: J1.10, R8.2, U8.37 (DIO_24)
VDD: C3.1, C8.1, C22.1, C25.1, C26.1, C28.1, C29.1, L2.2, R3.1, R6.1, R7.1, R8.1, U3.3 (~WP), U3.7 (~HOLD), U3.8 (VDD), U4.2 (CS_XL), U4.3 (CS_MAG), U4.9 (Vdd), U4.10 (Vdd_IO), U7.3 (~WP), U7.7 (~HOLD), U7.8 (Vcc), U8.13 (VDDS2), U8.22 (VDDS3), U8.44 (VDDS), U8.45 (VDDR), U8.48 (VDDR_RF)
VDDA: C9.1, C17.1, U5.5 (OUT), U9.3A (RLDIN), U9.4A (AVDD), U9.4B (AVDD), U9.6A (AVDD), U9.6B (AVDD), U9.6C (AVDD), U9.7A (AVDD1)
VSSA: C12.1, C13.2, C14.2, C15.2, C16.2, C18.2, C19.2, C23.1, C24.1, C27.1, CN2.5 (C4.2), CN2.6 (C3.2), CN2.7 (C2.2), CN2.8 (C1.2), CN3.5 (C4.2), CN3.6 (C3.2), CN3.7 (C2.2), CN3.8 (C1.2), R4.1, U6.5 (OUT), U9.4D (AVSS), U9.4H (VREFN), U9.5A (AVSS), U9.5B (AVSS), U9.5C (AVSS), U9.5D (AVSS), U9.8A (AVSS1)
_AXY_MAG: U4.7 (INT_MAG/DRDY), U8.10 (DIO_5)
_DEBUG: J2.6, U8.20 (DIO_14)
_EEG_CS: U8.31 (DIO_21), U9.7F (~CS)
_EEG_DRDY: U8.36 (DIO_23), U9.6D (~DRDY)
_FRAM_CS: U3.1 (~CS), U8.17 (DIO_11)
_NAND_CS: U7.1 (~CS), U8.30 (DIO_20)
_RESET: C11.1, J2.3, R3.2, U2.7 (PG), U8.35 (RESET_N)
~SHDN: U1.5 (~SHDN), U2.4 (CTRL), U5.3 (EN), U6.3 (EN), U8.26 (DIO_16), U9.5G (~PWDN), U9.6G (~RESET)

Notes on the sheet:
Vo=-1.186*(1+33000/63400)
(-1.5v)
(+1.5v)
(-1.8v)
Analog reference circuit (minimal power consumption)
EEG only
Review /Users/matt/Box Sync/Biologging/Technology/ESLO_RB/components/_MCU_RB/App Notes/PCB-Design_swra640e.pdf “CCFG to disable the DC/DC converter and supply VDDR from Global LDO”
CC2652RB: see PCB-Design_swra640e.pdf
LP SPI FLASH
SHARED
SHARED CAP
BTN1 BTN2
Shared 1uF cap
SHARED 2.2uF replaces 1uF
SHARED caps on VDD this remains ‘local’
LED is 3v, no R
or GNDD
Use int pull-up
LOW for DEBUG mode
!!Needs 1.8V for level shifters
10nF = 10000pF
GR LED SPI SPI SPI
*Need these for initial program/debug
UART UART
X These are actually 0.1uF, 1uF doesn’t exist
Tried replacing with 1M, voltage was inaccurate *200K across Vbatt = 13uA

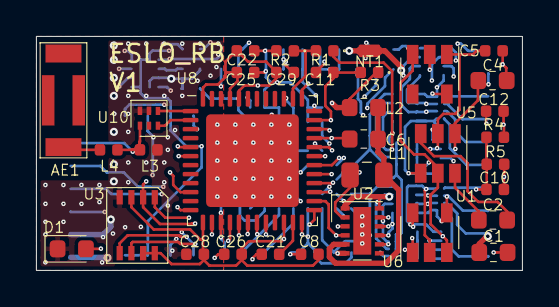
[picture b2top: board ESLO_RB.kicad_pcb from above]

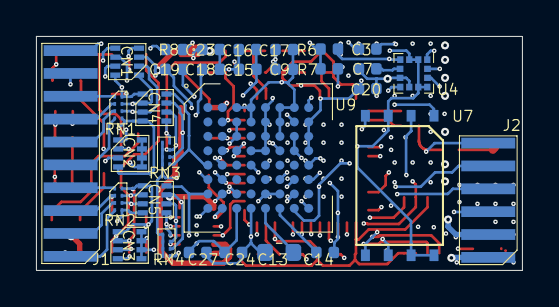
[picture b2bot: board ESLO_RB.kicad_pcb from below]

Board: 4 copper layers, 27.0 x 13.0 mm, 65 parts (31 on the bottom side), 74 nets.

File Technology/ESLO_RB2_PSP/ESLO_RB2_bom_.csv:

Component,Description,Part,References,Value,Footprint,Quantity Per PCB,Datasheet,Digikey,Mouser
1,Antenna,Antenna,AE1,2450AT42B100,2450AT42B100,1,~,712-1008-1-ND‎,
2,Unpolarized capacitor,C,C11 C17 C20 C22 C23 C25 C26 C28 C29,0.1uF,C_0402_1005Metric,9,~,490-6328-1-ND,
3,Unpolarized capacitor,C,C10,10nF,C_0402_1005Metric,1,~,1276-1051-1-ND,
4,Unpolarized capacitor,C,C2 C4,10uF,C_0603_1608Metric,2,~,478-10766-2-ND,
5,Unpolarized capacitor,C,C30 C31,12pF,C_0402_1005Metric,2,~,490-5924-2-ND,
6,Unpolarized capacitor,C,C3 C5 C21,1uF,C_0402_1005Metric,3,~,399-4873-1-ND,
7,Unpolarized capacitor,C,C1 C12,2.2uF,C_0402_1005Metric,2,~,GRM155R61E225KE11D,
8,Unpolarized capacitor,C,C6,4.7uF,C_0402_1005Metric,1,~,1276-1484-2-ND,
9,Light emitting diode,LED,D1 D2,LED,LED_0603_1608Metric,2,~,SML-D12V1WT86CT-ND,
10,"Generic connector, single row, 01x08, script generated (kicad-library-utils/schlib/autogen/connector/)",Conn_01x08_Female,J1 J2,Biopotentials,ESLO_IO_8_1-27,2,~,ED8250-ND ED90570-ND,
11,"Generic connector, single row, 01x02, script generated (kicad-library-utils/schlib/autogen/connector/)",Conn_01x02_Female,J3,Conn_01x02_Female,ESLO_2pin_THERM,1,~,,
12,Inductor,L,L3,1.5nH,L_0402_1005Metric,1,~,334-1083-2-ND,
13,Inductor,L,L1,2.2uH,L_0805_2012Metric,1,~,490-4994-2-ND,
14,Inductor,L,L4,3.3nH,L_0402_1005Metric,1,~,712-1416-1-ND,
15,"Net tie, 2 pins",Net-Tie_2,NT1,Net-Tie_2,NetTie-2_SMD_Pad0.5mm,1,~,,
16,Resistor,R,R1 R2 R3 R8,100k,LED_0402_1005Metric,4,~,311-100KLRCT-ND,
17,Resistor,R,R4,21.5k,R_0402_1005Metric,1,~,RMCF0402FT21K5CT-ND,
18,Resistor,R,R5,80.6k,R_0402_1005Metric,1,~,RMCF0402FT80K6CT-ND,
19,,2450BM14G0011,U10,2450BM14G0011,2450BM14G0011,1,,712-1620-1-ND,
20,,IS37SML01G1,U7,AS5F18G04SND-10LIN,8x6mm_WSON_UTSO,1,,1450-AS5F34G04SND-08LIN-ND,340-319932-REEL
21,,CC2652RB,U8,CC2652R1FRGZT,QFN-48-1EP_7x7mm_P0.5mm_EP5.15x5.15mm,1,,,595-CC2652R1FRGZR
22,"I2C/SPI, iNEMO inertial module: always-on 3D accelerometer and 3D gyroscope",LSM6DS3,U3,LSM6DSOXTR,LGA-14_3x2.5mm_P0.5mm_LayoutBorder3x4y,1,www.st.com/resource/en/datasheet/lsm6ds3.pdf,497-18367-2-ND,
23,,MAX1720,U1,MAX1720,SOT-23-6,1,,MAX1720EUTGOSCT-ND,
24,,TPS6223xx,U4,TPS6223xx,USON6-1.45x1.00mm-0.5pads,1,,296-39453-2-ND,
25,,TPS72325,U6,TPS72301DRVR,WSON-6-1EP_2x2mm_P0.65mm_EP1x1.6mm,1,,296-TPS72301DRVRTR-ND,
26,,TPS7A20_X2SON,U2,TPS7A2015PDQNR,Texas_X2SON-4_1x1mm_P0.65mm,1,,296-TPS7A2015PDQNRTR-ND,
27,Two pin crystal,Crystal,Y2,32.768kHz,Crystal_SMD_2012-2Pin_2.0x1.2mm,1,~,SER4081TR-ND,
28,"Four pin crystal, GND on pins 2 and 4",Crystal_GND24,Y1,48MHz,Crystal_SMD_2016-4Pin_2.0x1.6mm,1,~,535-13927-2-ND,





Component Groups:,28
Component Count:,46
Fitted Components:,46
Number of PCBs:,1
Total components:,46
Schematic Version:,
Schematic Date:,
BoM Date:,"Monday, May 03, 2021 at 05:46:10 PM"
Schematic Source:,/Users/matt/Box Sync/Biologging/Technology/ESLO_RB2_PSP/ESLO_RB2.sch
KiCad Version:,Eeschema (5.1.5-0-10_14)

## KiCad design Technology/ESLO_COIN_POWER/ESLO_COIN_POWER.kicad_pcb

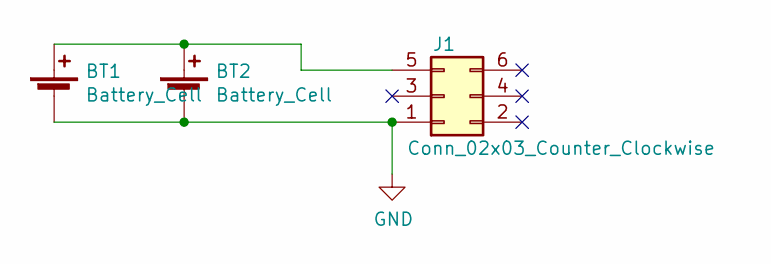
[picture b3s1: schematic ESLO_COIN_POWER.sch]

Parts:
BT1, BT2: Battery_Cell; BatteryHolder_Keystone_1060_1x2032; Digikey 36-1060-ND
J1: Conn_02x03_Counter_Clockwise; PinSocket_2x03_P2.54mm_Vertical; Digikey A106656-ND

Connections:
GND: BT1.2 (-), BT2.2 (-), J1.1
unnamed: BT1.1 (+), BT2.1 (+), J1.5
